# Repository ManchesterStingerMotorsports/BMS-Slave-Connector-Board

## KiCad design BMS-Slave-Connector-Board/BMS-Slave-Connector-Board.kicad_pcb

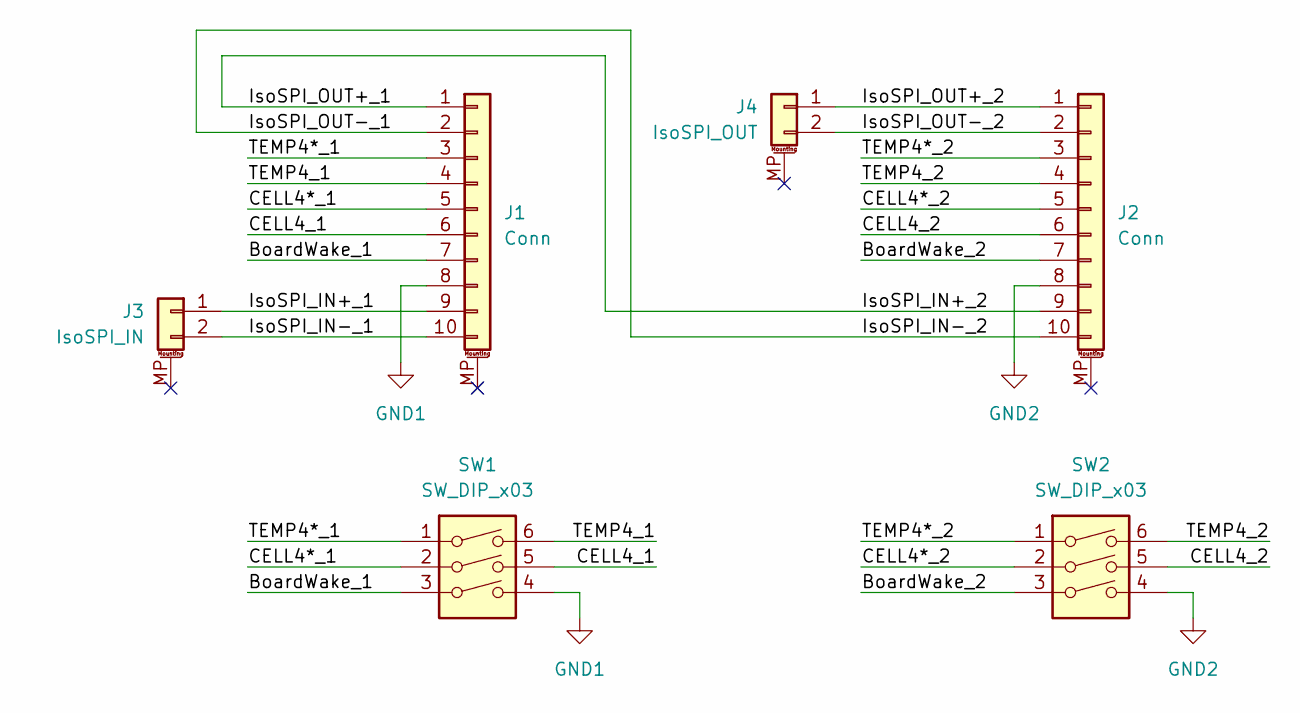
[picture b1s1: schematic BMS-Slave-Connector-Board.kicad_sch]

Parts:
J1, J2: Conn; 68711014522
J3: IsoSPI_IN; DuraClik_2POS-Vert
J4: IsoSPI_OUT; DuraClik_2POS-Vert
SW1, SW2: SW_DIP_x03; 418121270803

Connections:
/BoardWake_1: J1.7, SW1.3
/BoardWake_2: J2.7, SW2.3
/CELL4*_1: J1.5, SW1.2
/CELL4*_2: J2.5, SW2.2
/CELL4_1: J1.6, SW1.5
/CELL4_2: J2.6, SW2.5
/IsoSPI_IN+_1: J1.9, J3.1
/IsoSPI_IN+_2: J1.1, J2.9
/IsoSPI_IN-_1: J1.10, J3.2
/IsoSPI_IN-_2: J1.2, J2.10
/IsoSPI_OUT+_2: J2.1, J4.1
/IsoSPI_OUT-_2: J2.2, J4.2
/TEMP4*_1: J1.3, SW1.1
/TEMP4*_2: J2.3, SW2.1
/TEMP4_1: J1.4, SW1.6
/TEMP4_2: J2.4, SW2.6
GND1: J1.8, SW1.4
GND2: J2.8, SW2.4

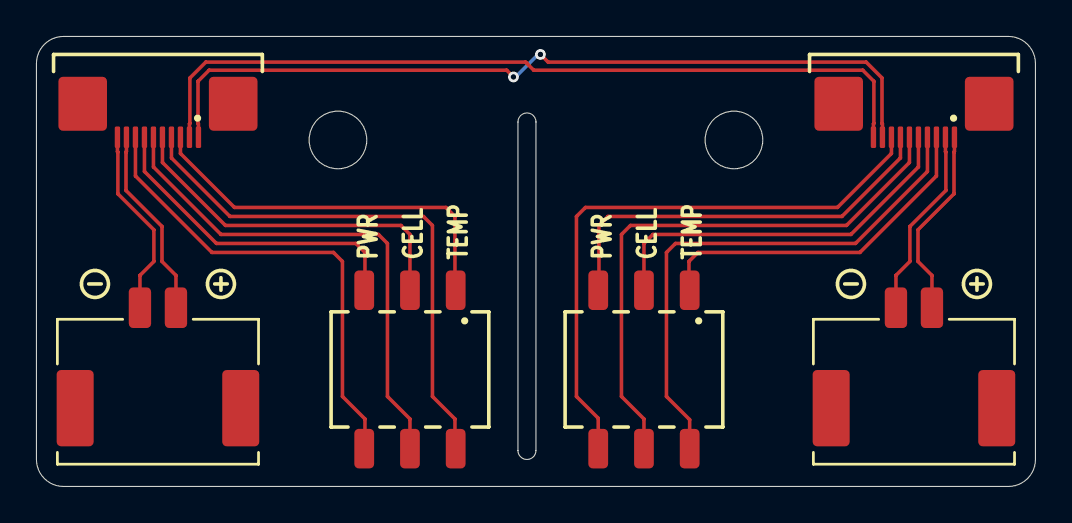
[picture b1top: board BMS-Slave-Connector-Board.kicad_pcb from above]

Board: 2 copper layers, 55.5 x 25.0 mm, 6 parts (0 on the bottom side), 18 nets.
